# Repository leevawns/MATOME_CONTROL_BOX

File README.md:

# MATOME_CONTROL_BOX
1. LED CARD
2. MAIN
3. LED MAU
4. LED JIGU
5. CODE ARDUINO MEGA FOR MATOME

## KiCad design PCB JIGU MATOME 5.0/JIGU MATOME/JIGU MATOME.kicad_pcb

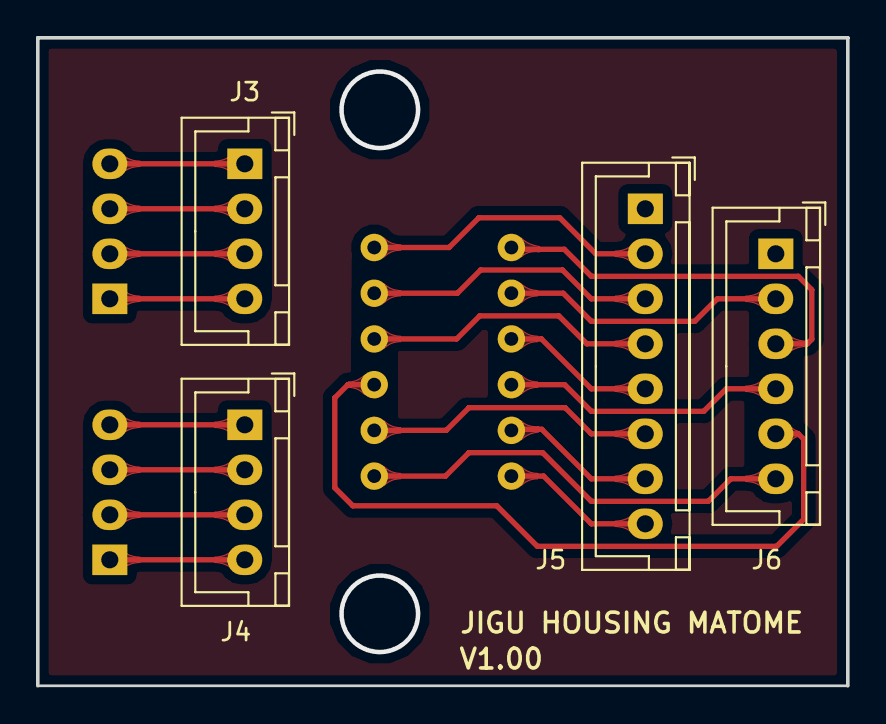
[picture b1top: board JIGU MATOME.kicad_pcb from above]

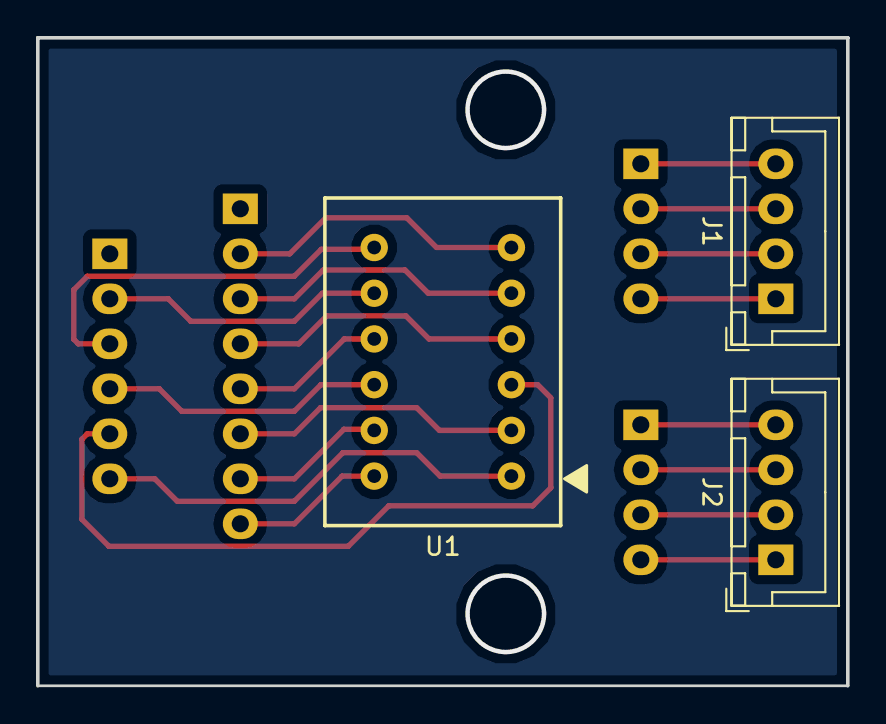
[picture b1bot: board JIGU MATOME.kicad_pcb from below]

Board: 2 copper layers, 45.0 x 36.0 mm, 7 parts (3 on the bottom side), 20 nets.

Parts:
J1, J2, J3, J4: Conn_01x04; JST_XH_B04B-XH-A_1x04_P2.50mm_Vertical
J5: Conn_01x08; JST_XH_B08B-XH-A_1x08_P2.50mm_Vertical
J6: Conn_01x06; JST_XH_B06B-XH-A_1x06_P2.50mm_Vertical
U1: 757BS

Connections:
unnamed: J1.1, J3.4
unnamed: J1.2, J3.3
unnamed: J1.3, J3.2
unnamed: J1.4, J3.1
unnamed: J2.1, J4.4
unnamed: J2.2, J4.3
unnamed: J2.3, J4.2
unnamed: J2.4, J4.1
unnamed: J5.2, U1.6
unnamed: J5.3, U1.5
unnamed: J5.4, U1.4
unnamed: J5.5, U1.9
unnamed: J5.6, U1.2
unnamed: J5.7, U1.11
unnamed: J5.8, U1.12
unnamed: J6.2, U1.8
unnamed: J6.3, U1.7
unnamed: J6.4, U1.10
unnamed: J6.5, U1.3
unnamed: J6.6, U1.1

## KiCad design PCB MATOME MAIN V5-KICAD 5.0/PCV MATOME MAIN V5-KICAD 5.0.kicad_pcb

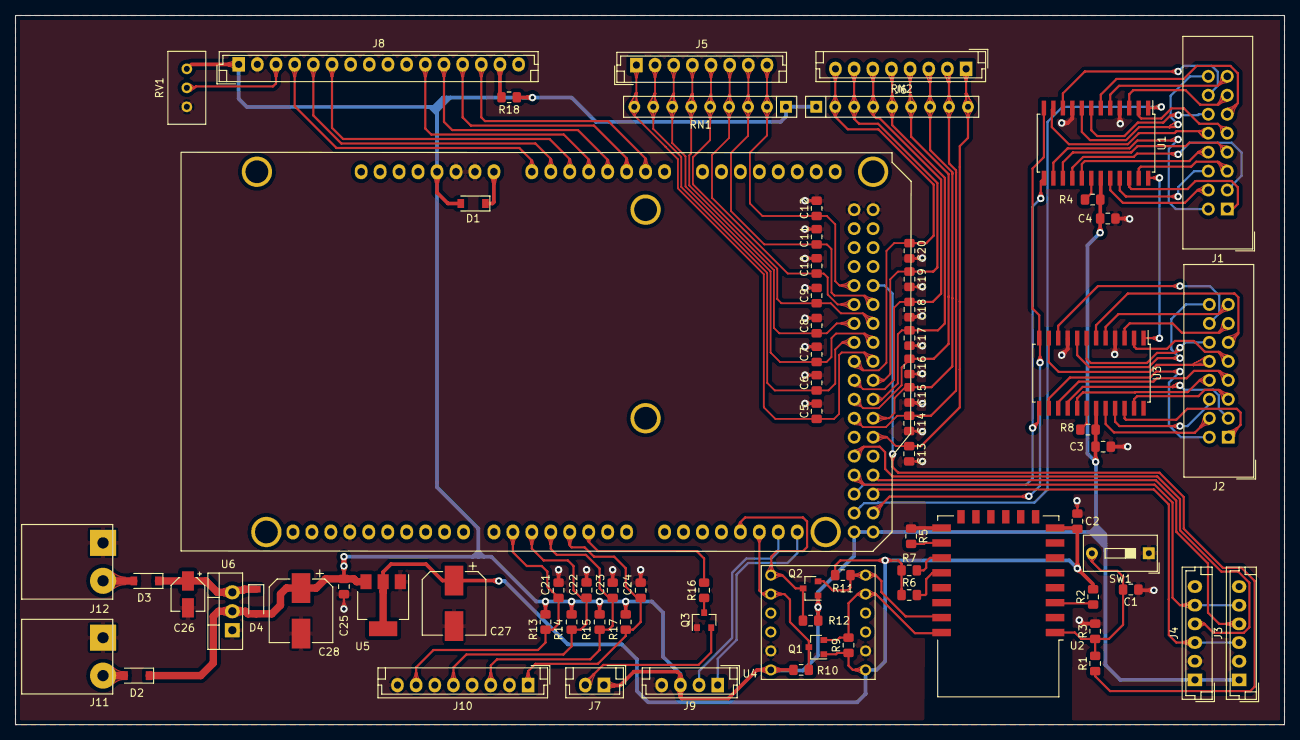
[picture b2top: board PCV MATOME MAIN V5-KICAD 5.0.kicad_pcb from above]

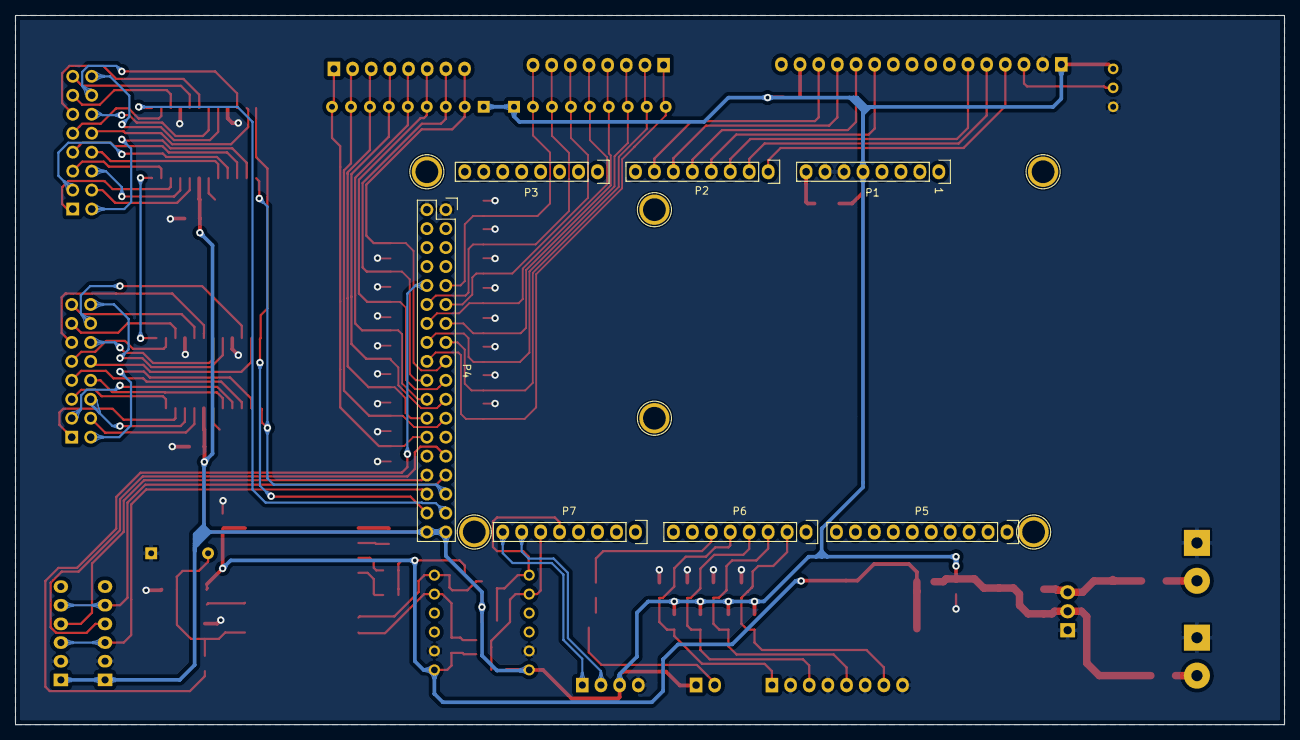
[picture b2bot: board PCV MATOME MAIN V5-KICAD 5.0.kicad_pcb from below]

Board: 2 copper layers, 170.0 x 95.0 mm, 88 parts (13 on the bottom side), 93 nets.

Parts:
C1, C2, C3, C4, C5, C6, C7, C8, C9, C10, C11, C12, C13, C14, C15, C16, C17, C18, C19, C20, C21, C22, C23, C24: 100n; C_0805_2012Metric_Pad1.15x1.40mm_HandSolder
C25: 10u; C_0805_2012Metric_Pad1.15x1.40mm_HandSolder
C26: 10u; CP_Elec_4x5.4
C27, C28: 100u; CP_Elec_8x6.5
D1, D2, D3, D4: D; D_SOD-123
J1, J2: Conn_02x08_Odd_Even; IDC-Header_2x08_P2.54mm_Vertical
J3, J4: Conn_01x06; JST_EH_B06B-EH-A_1x06_P2.50mm_Vertical
J5, J6, J10: Conn_01x08; JST_EH_B08B-EH-A_1x08_P2.50mm_Vertical
J7: Conn_01x02; JST_EH_B02B-EH-A_1x02_P2.50mm_Vertical
J8: Conn_01x16; JST_EH_B16B-EH-A_1x16_P2.50mm_Vertical
J9: Conn_01x04; JST_EH_B04B-EH-A_1x04_P2.50mm_Vertical
J11, J12: Conn_01x02; SolderWirePad_1x02_P5.08mm_Drill1.5mm
P1: Power; Socket_Strip_Arduino_1x08
P2, P3: Analog; Socket_Strip_Arduino_1x08
P4: Digital; Socket_Strip_Arduino_2x18
P5: PWM; Socket_Strip_Arduino_1x10
P6: PWM; Socket_Strip_Arduino_1x08
P7: Communication; Socket_Strip_Arduino_1x08
P8, P9, P10, P11, P12, P13: CONN_01X01; Arduino_1pin
Q1, Q2: BSS138; SOT-23
Q3: 2SC1815; SOT-23
R1, R2, R4, R5, R6, R7, R8, R9, R10, R11, R12, R13, R14, R15, R16, R17: 10K; R_0805_2012Metric_Pad1.15x1.40mm_HandSolder
R3: 20K; R_0805_2012Metric_Pad1.15x1.40mm_HandSolder
R18: 100; R_0805_2012Metric_Pad1.15x1.40mm_HandSolder
RN1, RN2: R_Network08; R_Array_SIP9
RV1: R_POT; Potentiometer_Bourns_3296W_Vertical
SW1: SW_Push; SW_DIP_SPSTx01_Slide_9.78x4.72mm_W7.62mm_P2.54mm
U1, U3: MAX7219; SOIC-24W_7.5x15.4mm_P1.27mm
U2: ESP-12F; ESP-12E
U4: SHIFT_LEVEL_3.3V_5V; SHIFTLEVEL
U5: LM1117-3.3; SOT-223-3_TabPin2
U6: LD1117S50TR_SOT223; TO-220-3_Vertical

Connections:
1-C1: J1.1, U1.22
1-C2: J1.2, U1.14
1-C3: J1.3, U1.16
1-C4: J1.4, U1.20
1-C5: J1.5, U1.23
1-C6: J1.6, U1.21
1-C7: J1.7, U1.15
1-C8: J1.8, U1.17
1-R1: J1.9, U1.2
1-R2: J1.10, U1.11
1-R3: J1.11, U1.6
1-R4: J1.12, U1.7
1-R5: J1.13, U1.3
1-R6: J1.14, U1.10
1-R7: J1.15, U1.5
1-R8: J1.16, U1.8
2-C1: J2.1, U3.22
2-C2: J2.2, U3.14
2-C3: J2.3, U3.16
2-C4: J2.4, U3.20
2-C5: J2.5, U3.23
2-C6: J2.6, U3.21
2-C7: J2.7, U3.15
2-C8: J2.8, U3.17
2-R1: J2.9, U3.2
2-R2: J2.10, U3.11
2-R3: J2.11, U3.6
2-R4: J2.12, U3.7
2-R5: J2.13, U3.3
2-R6: J2.14, U3.10
2-R7: J2.15, U3.5
2-R8: J2.16, U3.8
/Vin: D1.1, P1.8
BACK: C23.1, J10.3, P6.4, R15.1
BUZZER: P6.6, R16.2
CLK_M: P4.31, U1.13, U3.13
D4: J8.11, P2.4
D5: J8.12, P2.5
D6: J8.13, P2.6
D7: J8.14, P2.7
DIN: J3.3, J4.3, P4.32
DIN_M: P4.33, U1.1
EN: J8.6, P2.3
HOME: C22.1, J10.5, P6.3, R14.1
HV: C3.2, C4.2, C25.1, C28.1, D1.2, D2.1, D4.2, J3.1, J4.1, J7.1, J8.1, J9.3, P1.5, P4.35, P4.36, Q2.1, R4.1, R8.1, R10.1, R12.1, R13.2, R14.2, R15.2, R17.2, R18.1, RN1.1, RN2.1, RV1.1, U1.19, U3.19, U4.12, U5.3, U6.2
LV: C2.1, C27.1, Q1.1, R2.2, R6.1, R7.1, R9.1, R11.1, U2.8, U4.1, U5.2
NEXT: C24.1, J10.1, P6.5, R17.1
unnamed: C1.1, C2.2, C3.1, C4.1, C5.2, C6.2, C7.2, C8.2, C9.2, C10.2, C11.2, C12.2, C13.2, C14.2, C15.2, C16.2, C17.2, C18.2, C19.2, C20.2, C21.2, C22.2, C23.2, C24.2, C25.2, C26.2, C27.2, C28.2, J3.2, J4.2, J8.2, J9.4, J10.2, J10.4, J10.6, J10.8, J11.1, J12.1, P1.6, P1.7, P4.1, P4.2, P5.4, Q3.1, R3.2, R5.1, RV1.3, SW1.1, U1.4, U1.9, U2.15, U3.4, U3.9, U4.2, U4.11, U5.1, U6.1
unnamed: C1.2, R1.2, R3.1, SW1.2, U2.1
unnamed: C26.1, D3.1, D4.1, U6.3
unnamed: D2.2, J11.2
unnamed: D3.2, J12.2
unnamed: J7.2, Q3.2
unnamed: J8.3, RV1.2
unnamed: J8.15, R18.2
unnamed: Q3.3, R16.1
unnamed: R2.1, U2.3
unnamed: R4.2, U1.18
unnamed: R5.2, U2.16
unnamed: R6.2, U2.18
unnamed: R7.2, U2.17
unnamed: R8.2, U3.18
unnamed: U1.24, U3.1
RESET_ESP: P4.10, R1.1
RS: J8.4, P2.1
RW: J8.5, P2.2
RX3.3V: Q2.2, R11.2, U2.21, U4.6
RX5V: P7.5, Q2.3, R12.2, U4.7
SC1: J3.4, P4.30
SC2: J4.4, P4.27
SCK: J3.5, J4.5, P4.29
SCL: J9.1, P7.8
SC_M: P4.34, U1.12, U3.12
SDA: J9.2, P7.7
SET: C21.1, J10.7, P6.2, R13.1
SW1: C13.1, J6.1, P4.26, RN2.9
SW2: C14.1, J6.2, P4.23, RN2.8
SW3: C15.1, J6.3, P4.24, RN2.7
SW4: C16.1, J6.4, P4.21, RN2.6
SW5: C17.1, J6.5, P4.22, RN2.5
SW6: C18.1, J6.6, P4.19, RN2.4
SW7: C19.1, J6.7, P4.20, RN2.3
SW8: C20.1, J6.8, P4.17, RN2.2
SW9: C5.1, J5.1, P4.18, RN1.9
SW10: C6.1, J5.2, P4.15, RN1.8
SW11: C7.1, J5.3, P4.16, RN1.7
SW12: C8.1, J5.4, P4.13, RN1.6
SW13: C9.1, J5.5, P4.14, RN1.5
SW14: C10.1, J5.6, P4.11, RN1.4
SW15: C11.1, J5.7, P4.12, RN1.3
SW16: C12.1, J5.8, P4.9, RN1.2
TX3.3V: Q1.2, R9.2, U2.22, U4.5
TX5V: P7.6, Q1.3, R10.2, U4.8

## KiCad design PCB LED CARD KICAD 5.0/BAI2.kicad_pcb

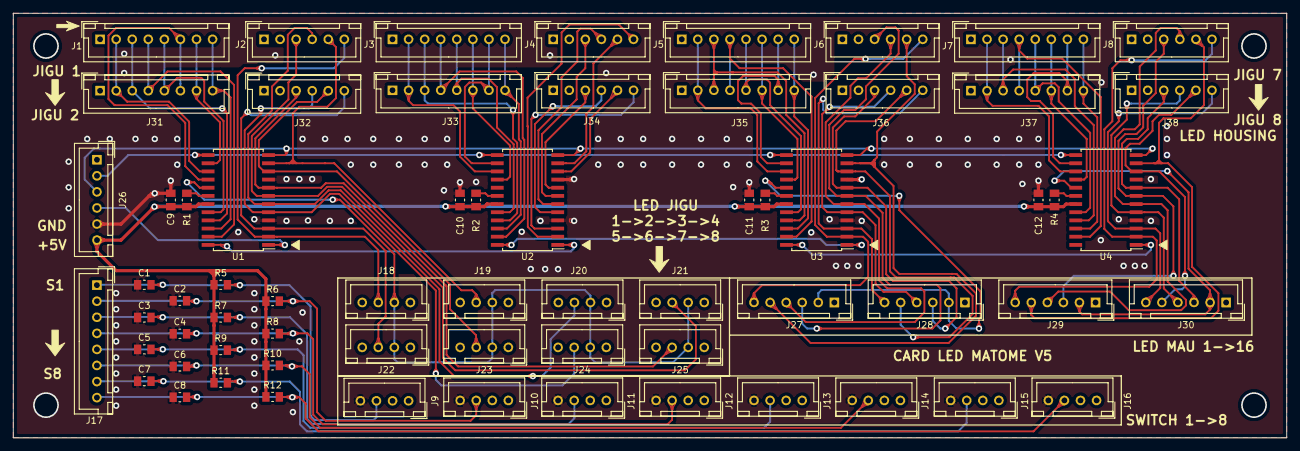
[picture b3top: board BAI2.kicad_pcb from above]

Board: 2 copper layers, 198.1 x 66.0 mm, 66 parts (0 on the bottom side), 83 nets.

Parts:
C1, C2, C3, C4, C5, C6, C7, C8, C9, C10, C11, C12: 100n; C_0805_2012Metric_Pad1.15x1.50mm_HandSolder
J1, J3, J5, J7, J17, J31, J33, J35, J37: Conn_01x08; JST_XH_B08B-XH-A_08x2.50mm_Straight
J2, J4, J6, J8, J26, J27, J28, J29, J30, J32, J34, J36, J38: Conn_01x06; JST_XH_B06B-XH-A_06x2.50mm_Straight
J9, J10, J11, J12, J13, J14, J15, J16, J18, J19, J20, J21, J22, J23, J24, J25: Conn_01x04; JST_XH_B04B-XH-A_04x2.50mm_Straight
R1, R2, R3, R4, R5, R6, R7, R8, R9, R10, R11, R12: 10K; R_0805_2012Metric_Pad1.15x1.50mm_HandSolder
U1, U2, U3, U4: MAX7219; SOIC-24W_7.5x15.4mm_Pitch1.27mm

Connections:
+5V: C9.1, C10.1, C11.1, C12.1, J26.6, R1.1, R2.1, R3.1, R4.1, R5.1, R6.1, R7.1, R8.1, R9.1, R10.1, R11.1, R12.1, U1.19, U2.19, U3.19, U4.19
/1-C1: J1.8, J31.8, U1.22
/1-C2: J1.7, J31.7, U1.14
/1-C3: J1.6, J31.6, U1.16
/1-C4: J1.5, J31.5, U1.20
/1-C5: J1.4, J31.4, U1.23
/1-C6: J1.3, J31.3, U1.21
/1-C7: J1.2, J31.2, U1.15
/1-C8: J18.2, J19.2, J20.2, J21.2, J22.2, J23.2, J24.2, J25.2, U1.17
/1-R1: J2.6, J18.3, U1.2
/1-R2: J2.5, J19.3, U1.11
/1-R3: J2.4, J20.3, U1.6
/1-R4: J2.3, J21.3, U1.7
/1-R5: J22.3, J32.6, U1.3
/1-R6: J23.3, J32.5, U1.10
/1-R7: J24.3, J32.4, U1.5
/1-R8: J25.3, J32.3, U1.8
/2-C1: J3.8, J33.8, U2.22
/2-C2: J3.7, J33.7, U2.14
/2-C3: J3.6, J33.6, U2.16
/2-C4: J3.5, J33.5, U2.20
/2-C5: J3.4, J33.4, U2.23
/2-C6: J3.3, J33.3, U2.21
/2-C7: J3.2, J33.2, U2.15
/2-R1: J4.6, U2.2
/2-R2: J4.5, U2.11
/2-R3: J4.4, U2.6
/2-R4: J4.3, U2.7
/2-R5: J34.6, U2.3
/2-R6: J34.5, U2.10
/2-R7: J34.4, U2.5
/2-R8: J34.3, U2.8
/3-C1: J5.8, J35.8, U3.22
/3-C2: J5.7, J35.7, U3.14
/3-C3: J5.6, J35.6, U3.16
/3-C4: J5.5, J35.5, U3.20
/3-C5: J5.4, J35.4, U3.23
/3-C6: J5.3, J35.3, U3.21
/3-C7: J5.2, J35.2, U3.15
/3-C8: J27.2, J28.2, U3.17
/3-R1: J6.6, J27.6, U3.2
/3-R2: J6.5, J27.5, U3.11
/3-R3: J6.4, J27.4, U3.6
/3-R4: J6.3, J27.3, U3.7
/3-R5: J28.6, J36.6, U3.3
/3-R6: J28.5, J36.5, U3.10
/3-R7: J28.4, J36.4, U3.5
/3-R8: J28.3, J36.3, U3.8
/4-C1: J7.8, J37.8, U4.22
/4-C2: J7.7, J37.7, U4.14
/4-C3: J7.6, J37.6, U4.16
/4-C4: J7.5, J37.5, U4.20
/4-C5: J7.4, J37.4, U4.23
/4-C6: J7.3, J37.3, U4.21
/4-C7: J7.2, J37.2, U4.15
/4-C8: J29.2, J30.2, U4.17
/4-R1: J8.6, J29.6, U4.2
/4-R2: J8.5, J29.5, U4.11
/4-R3: J8.4, J29.4, U4.6
/4-R4: J8.3, J29.3, U4.7
/4-R5: J30.6, J38.6, U4.3
/4-R6: J30.5, J38.5, U4.10
/4-R7: J30.4, J38.4, U4.5
/4-R8: J30.3, J38.3, U4.8
/CLK: J26.2, U1.13, U2.13, U3.13, U4.13
/CS: J26.3, U1.12, U2.12, U3.12, U4.12
/DIN: J26.4, U1.1
/SW1: C1.2, J9.3, J17.1, R5.2
/SW2: C2.2, J10.3, J17.2, R6.2
/SW3: C3.2, J11.3, J17.3, R7.2
/SW4: C4.2, J12.3, J17.4, R8.2
/SW5: C5.2, J13.3, J17.5, R9.2
/SW6: C6.2, J14.3, J17.6, R10.2
/SW7: C7.2, J15.3, J17.7, R11.2
/SW8: C8.2, J16.3, J17.8, R12.2
unnamed: R1.2, U1.18
unnamed: R2.2, U2.18
unnamed: R3.2, U3.18
unnamed: R4.2, U4.18
unnamed: U1.24, U2.1
unnamed: U2.24, U3.1
unnamed: U3.24, U4.1
VSS: C1.1, C2.1, C3.1, C4.1, C5.1, C6.1, C7.1, C8.1, C9.2, C10.2, C11.2, C12.2, J9.4, J10.4, J11.4, J12.4, J13.4, J14.4, J15.4, J16.4, J26.5, U1.4, U1.9, U2.4, U2.9, U3.4, U3.9, U4.4, U4.9

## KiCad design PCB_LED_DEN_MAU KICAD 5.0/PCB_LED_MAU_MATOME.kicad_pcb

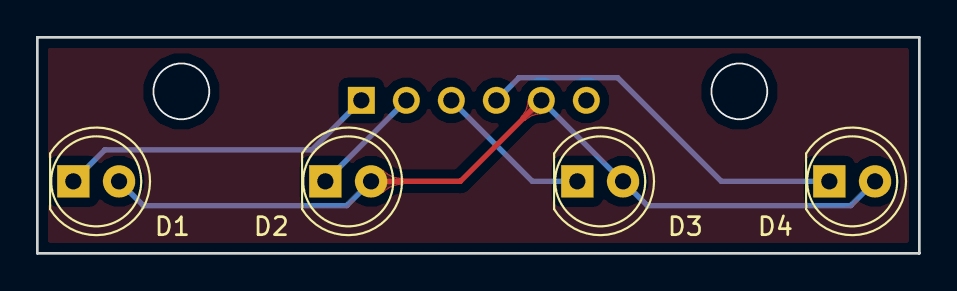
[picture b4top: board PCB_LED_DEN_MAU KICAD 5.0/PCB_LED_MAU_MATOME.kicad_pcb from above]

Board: 2 copper layers, 49.0 x 12.0 mm, 5 parts (1 on the bottom side), 5 nets.

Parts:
D1, D2, D3, D4: LED; LED_D5.0mm
J1: Conn_01x06; JST_XH_B06B-XH-A_06x2.50mm_Straight

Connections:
unnamed: D1.1, J1.1
unnamed: D1.2, D2.2, D3.2, D4.2, J1.5
unnamed: D2.1, J1.2
unnamed: D3.1, J1.3
unnamed: D4.1, J1.4

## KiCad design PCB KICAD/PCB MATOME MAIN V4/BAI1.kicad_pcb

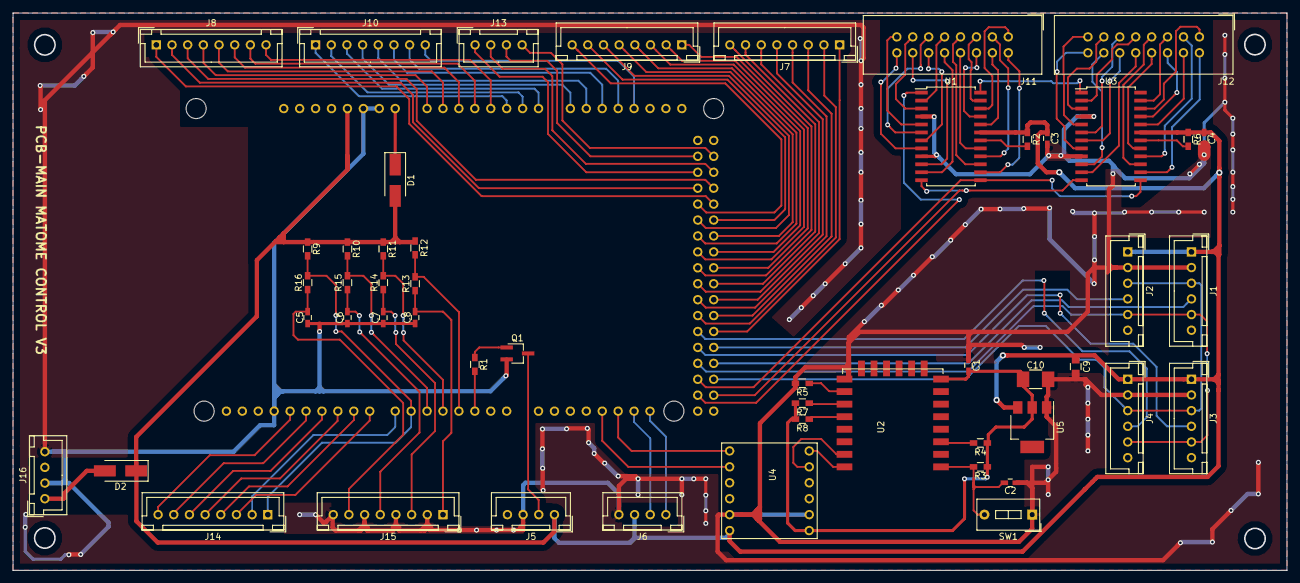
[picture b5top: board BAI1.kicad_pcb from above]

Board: 2 copper layers, 203.2 x 88.9 mm, 52 parts (1 on the bottom side), 114 nets.

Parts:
ARD1: Arduino_Mega2560_Shield
C1, C2, C3, C4, C5, C6, C7, C8: 100n; C_0603_HandSoldering
C9: 10u; C_0805_HandSoldering
C10: 100U; C_1210_HandSoldering
D1, D2: D; D_SMA_Handsoldering
J1, J2, J3, J4: Conn_01x06; JST_XH_B06B-XH-A_06x2.50mm_Straight
J5, J6, J13, J16: Conn_01x04; JST_XH_B04B-XH-A_04x2.50mm_Straight
J7, J8, J9, J10, J14, J15: Conn_01x08; JST_XH_B08B-XH-A_08x2.50mm_Straight
J11, J12: Conn_02x08_Odd_Even; IDC-Header_2x08_P2.54mm_Vertical
Q1: 2SC1815; TSOT-23_HandSoldering
R1, R2, R3, R4: 10K; R_0603_HandSoldering
R5, R6, R7, R8, R9, R10, R11, R12: 10k; R_0603_HandSoldering
R13: 470R; R_0603_HandSoldering
R14, R15, R16: 470; R_0603_HandSoldering
SW1: SW_Push; SW_DIP_x1_W7.62mm_Slide
U1, U3: MAX7219; SOIC-24W_7.5x15.4mm_Pitch1.27mm
U2: ESP-12E; ESP-12E_SMD
U4: logic_level; SHIFTLEVEL
U5: LM1117-3.3; SOT-223

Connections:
3.3V: C1.2, C10.1, R3.1, R4.1, R7.2, R8.2, U2.8, U4.7, U5.2
/1-C1: J11.1, U1.22
/1-C2: J11.2, U1.14
/1-C3: J11.3, U1.16
/1-C4: J11.4, U1.20
/1-C5: J11.5, U1.23
/1-C6: J11.6, U1.21
/1-C7: J11.7, U1.15
/1-C8: J11.8, U1.17
/1-R1: J11.9, U1.2
/1-R2: J11.10, U1.11
/1-R3: J11.11, U1.6
/1-R4: J11.12, U1.7
/1-R5: J11.13, U1.3
/1-R6: J11.14, U1.10
/1-R7: J11.15, U1.5
/1-R8: J11.16, U1.8
/2-C1: J12.1, U3.22
/2-C2: J12.2, U3.14
/2-C3: J12.3, U3.16
/2-C4: J12.4, U3.20
/2-C5: J12.5, U3.23
/2-C6: J12.6, U3.21
/2-C7: J12.7, U3.15
/2-C8: J12.8, U3.17
/2-R1: J12.9, U3.2
/2-R2: J12.10, U3.11
/2-R3: J12.11, U3.6
/2-R4: J12.12, U3.7
/2-R5: J12.13, U3.3
/2-R6: J12.14, U3.10
/2-R7: J12.15, U3.5
/2-R8: J12.16, U3.8
/BACK: ARD1.D4, R11.2, R14.2
/BUZ: ARD1.D2, R1.2
/CLK_M: ARD1.D24, U1.13, U3.13
/DIN: ARD1.D25, J1.3, J2.3, J3.3, J4.3
/DIN_M: ARD1.D22, U1.1
/HOME: ARD1.D5, R10.2, R15.2
/NEXT: ARD1.D3, R12.2, R13.2
/RXD1: ARD1.D19, U4.6
/SC1: ARD1.D27, J1.4
/SC2: ARD1.D28, J3.4
/SC3: ARD1.D29, J2.4
/SC4: ARD1.D30, J4.4
/SCK: ARD1.D26, J1.5, J2.5, J3.5, J4.5
/SCL: ARD1.D21, J6.1
/SC_M: ARD1.D23, U1.12, U3.12
/SDA: ARD1.D20, J6.2
/SET: ARD1.D6, J14.1, R9.2, R16.2
/SW1: ARD1.D31, J7.1
/SW2: ARD1.D32, J7.2
/SW3: ARD1.D33, J7.3
/SW4: ARD1.D34, J7.4
/SW5: ARD1.D35, J7.5
/SW6: ARD1.D36, J7.6
/SW7: ARD1.D37, J7.7
/SW8: ARD1.D38, J7.8
/SW9: ARD1.D39, J9.1
/SW10: ARD1.D40, J9.2
/SW11: ARD1.D41, J9.3
/SW12: ARD1.D42, J9.4
/SW13: ARD1.D43, J9.5
/SW14: ARD1.D44, J9.6
/SW15: ARD1.D45, J9.7
/SW16: ARD1.D46, J9.8
/SW17: ARD1.D47, J8.1
/SW18: ARD1.D48, J8.2
/SW19: ARD1.D49, J8.3
/SW20: ARD1.A0, J8.4
/SW21: ARD1.A1, J8.5
/SW22: ARD1.A2, J8.6
/SW23: ARD1.A3, J8.7
/SW24: ARD1.A4, J8.8
/SW25: ARD1.A5, J10.1
/SW26: ARD1.A6, J10.2
/SW27: ARD1.A7, J10.3
/SW28: ARD1.A8, J10.4
/SW29: ARD1.A9, J10.5
/SW30: ARD1.A10, J10.6
/SW31: ARD1.A11, J10.7
/SW32: ARD1.A12, J10.8
/TXD1: ARD1.D18, U4.5
unnamed: ARD1.D7, J14.2
unnamed: ARD1.D8, J14.3
unnamed: ARD1.D9, J14.4
unnamed: ARD1.D10, J14.5
unnamed: ARD1.D11, J14.6
unnamed: ARD1.D12, J14.7
unnamed: ARD1.D13, J14.8
unnamed: ARD1.D50, J13.1
unnamed: ARD1.D51, J13.2
unnamed: ARD1.D52, J13.3
unnamed: ARD1.D53, J13.4
unnamed: ARD1.VIN, D1.1
unnamed: C2.2, R3.2, SW1.2, U2.1
unnamed: C5.2, J15.7, R16.1
unnamed: C6.2, J15.5, R15.1
unnamed: C7.2, J15.3, R14.1
unnamed: C8.2, J15.1, R13.1
unnamed: D2.2, J16.1
unnamed: J5.2, Q1.3
unnamed: Q1.1, R1.1
unnamed: R2.2, U1.18
unnamed: R4.2, U2.3
unnamed: R5.1, U2.10
unnamed: R6.2, U3.18
unnamed: R7.1, U2.11
unnamed: R8.1, U2.12
unnamed: U1.24, U3.1
unnamed: U2.15, U4.11
unnamed: U2.16, U4.12
VDD: ARD1.5V1, C3.1, C4.1, C9.1, D1.2, D2.1, J1.1, J2.1, J3.1, J4.1, J5.1, J6.3, R2.1, R6.1, R9.1, R10.1, R11.1, R12.1, U1.19, U3.19, U4.1, U5.3
VSS: ARD1.GND1, ARD1.GND2, ARD1.GND3, C1.1, C2.1, C3.2, C4.2, C5.1, C6.1, C7.1, C8.1, C9.2, C10.2, J1.2, J2.2, J3.2, J4.2, J5.3, J6.4, J15.2, J15.4, J15.6, J15.8, J16.2, J16.4, Q1.2, R5.2, SW1.1, U1.4, U1.9, U2.9, U3.4, U3.9, U4.2, U4.8, U5.1

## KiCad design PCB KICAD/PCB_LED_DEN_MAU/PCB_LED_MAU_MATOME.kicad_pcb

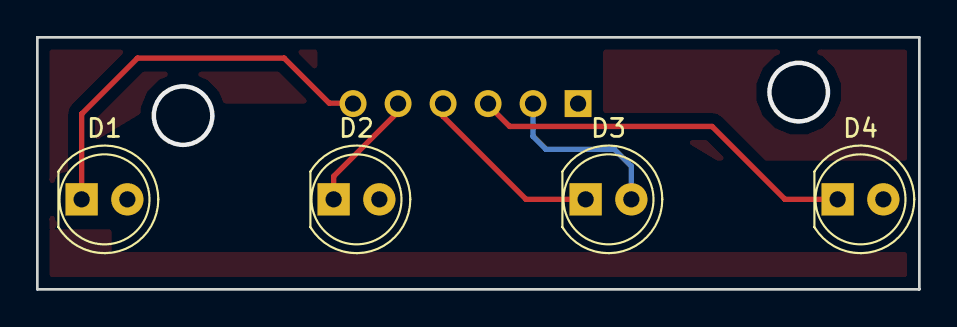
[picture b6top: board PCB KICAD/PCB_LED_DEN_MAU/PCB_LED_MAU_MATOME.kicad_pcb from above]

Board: 2 copper layers, 49.0 x 14.0 mm, 5 parts (1 on the bottom side), 5 nets.

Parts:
D1, D2, D3, D4: LED; LED_D5.0mm
J1: Conn_01x06; JST_XH_B06B-XH-A_06x2.50mm_Straight

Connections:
unnamed: D1.1, J1.6
unnamed: D1.2, D2.2, D3.2, D4.2, J1.2
unnamed: D2.1, J1.5
unnamed: D3.1, J1.4
unnamed: D4.1, J1.3

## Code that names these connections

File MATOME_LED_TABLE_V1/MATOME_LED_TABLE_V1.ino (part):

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#define S32 A12
//------------------------------------------------
#define buzer 4
#define next 5
#define back 6
#define reset 7
//#define frequency 560 //not use change to fix buzzer.
//------------------------------------------------
LiquidCrystal_I2C lcd(0x3F,20,4);
//-----------------------------------------------------
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//-------------------------------
    pinMode(buzer,OUTPUT);
    digitalWrite(buzer,HIGH);//fix to high
    pinMode(next,INPUT_PULLUP);
    pinMode(back,INPUT_PULLUP);
    pinMode(reset,INPUT_PULLUP);
//-------------------------------
    enableInterrupt(next,next_function,CHANGE);
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
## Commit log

2018-03-02 change name folder
2018-03-02 change all file
2018-03-02 add all file PCB
2018-07-31 initilize project
    beginning...
2018-08-01 mofifile 08012018
2018-08-02 finish schematic
2018-08-06 initinal pcb
2018-08-07 initilize pcb layout
2018-08-08 repairt schematic, layout pcb
2018-08-11 modifier pcb and schematic net list
2018-08-16 wiring pcb outline
2018-08-18 modified pcb 18/08/2018, test pcb final befor release
2018-08-18 testing gerber first, add teardrop
2018-08-18 add pcb led mau
2018-08-20 add led mau folder
2018-08-20 add PCB JIGU MATOME
2018-08-22 modifier pcb jigu
2018-09-18 modifier pcb carled
2018-09-18 modifier code arduino fix some bug for new matome insert machine
2018-09-22 fix library
2018-10-14 del old folder
2018-10-14 del folder old v4
